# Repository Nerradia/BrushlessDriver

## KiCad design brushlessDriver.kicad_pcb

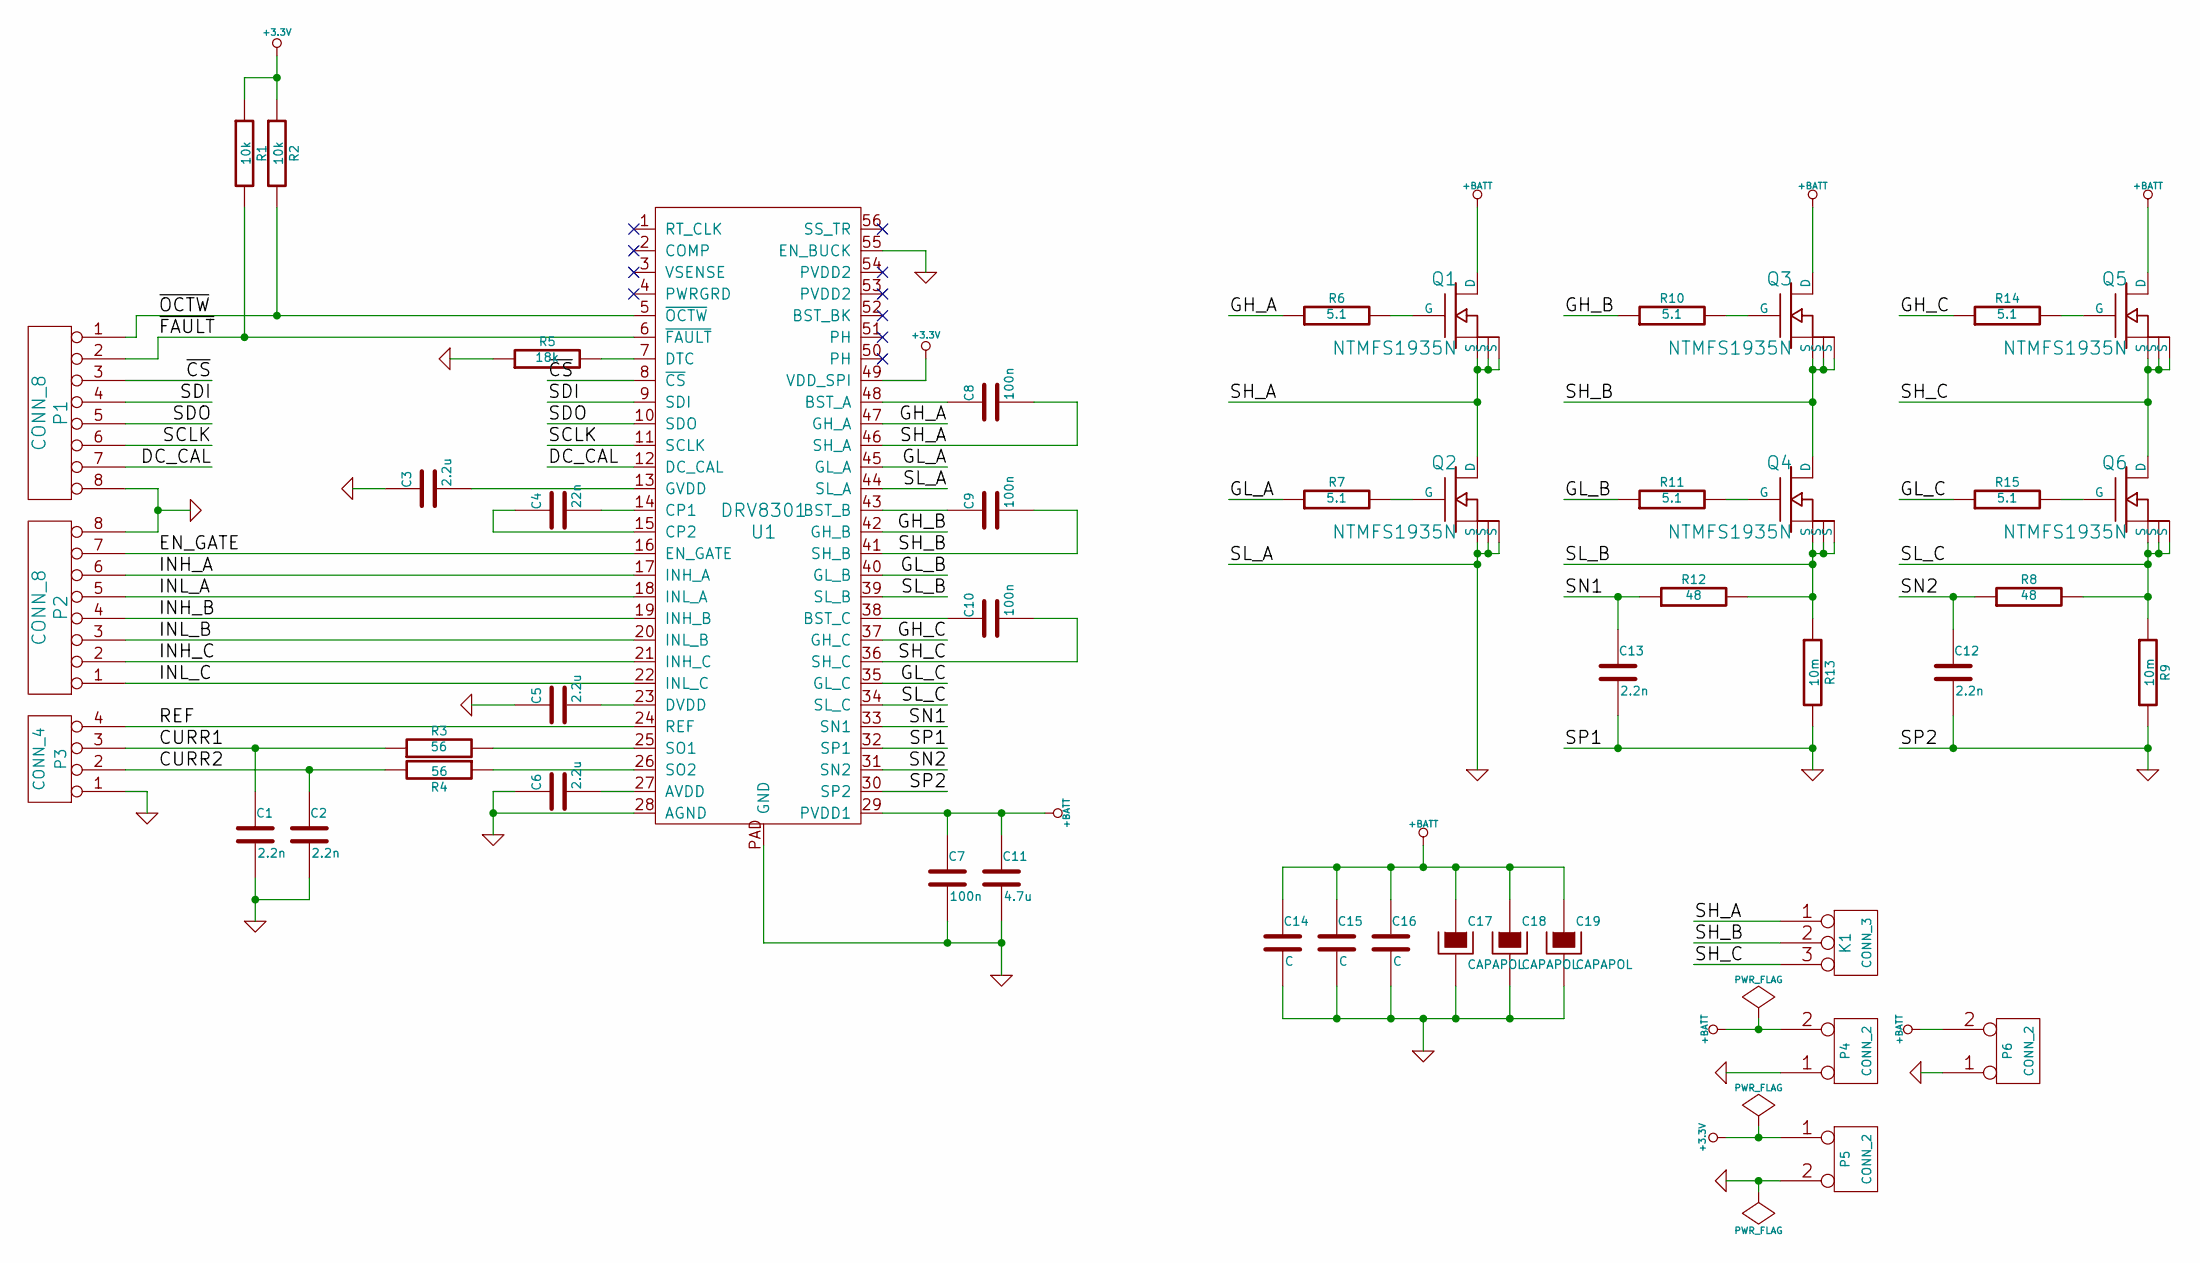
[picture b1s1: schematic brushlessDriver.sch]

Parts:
C1, C2, C12, C13: 2.2n
C3, C5, C6: 2.2u
C4: 22n
C7, C8, C9, C10: 100n
C11: 4.7u
C14, C15, C16: C
C17, C18, C19: CAPAPOL
K1: CONN_3
P1, P2: CONN_8
P3: CONN_4
P4, P5, P6: CONN_2
Q1, Q2, Q3, Q4, Q5, Q6: NTMFS1935N
R1, R2: 10k
R3, R4: 56
R5: 18k
R6, R7, R10, R11, R14, R15: 5.1
R8, R12: 48
R9, R13: 10m
U1: DRV8301

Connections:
+3.3V: P5.1, R1.1, R2.1, U1.49 (VDD_SPI)
+BATT: C7.1, C11.1, C14.1, C15.1, C16.1, C17.1, C18.1, C19.1, P4.2 (PM), P6.2 (PM), Q1.5 (D), Q3.5 (D), Q5.5 (D), U1.29 (PVDD1)
/CURR1: C1.1, P3.3, R3.1
/CURR2: C2.1, P3.2, R4.2
/DC_CAL: P1.7, U1.12 (DC_CAL)
/EN_GATE: P2.7, U1.16 (EN_GATE)
/GH_A: R6.1, U1.47 (GH_A)
/GH_B: R10.1, U1.42 (GH_B)
/GH_C: R14.1, U1.37 (GH_C)
/GL_A: R7.1, U1.45 (GL_A)
/GL_B: R11.1, U1.40 (GL_B)
/GL_C: R15.1, U1.35 (GL_C)
/INH_A: P2.6, U1.17 (INH_A)
/INH_B: P2.4, U1.19 (INH_B)
/INH_C: P2.2, U1.21 (INH_C)
/INL_A: P2.5, U1.18 (INL_A)
/INL_B: P2.3, U1.20 (INL_B)
/INL_C: P2.1, U1.22 (INL_C)
/REF: P3.4, U1.24 (REF)
/SCLK: P1.6, U1.11 (SCLK)
/SDI: P1.4, U1.9 (SDI)
/SDO: P1.5, U1.10 (SDO)
/SH_A: C8.2, K1.1, Q1.1 (S), Q1.2 (S), Q1.3 (S), Q2.5 (D), U1.46 (SH_A)
/SH_B: C9.2, K1.2 (PM), Q3.1 (S), Q3.2 (S), Q3.3 (S), Q4.5 (D), U1.41 (SH_B)
/SH_C: C10.2, K1.3, Q5.1 (S), Q5.2 (S), Q5.3 (S), Q6.5 (D), U1.36 (SH_C)
/SL_B: Q4.1 (S), Q4.2 (S), Q4.3 (S), R12.2, R13.1, U1.39 (SL_B)
/SL_C: Q6.1 (S), Q6.2 (S), Q6.3 (S), R8.2, R9.1, U1.34 (SL_C)
/SN1: C13.1, R12.1, U1.33 (SN1)
/SN2: C12.1, R8.1, U1.31 (SN2)
/~CS: P1.3, U1.8 (~CS)
/~FAULT: P1.2, R1.2, U1.6 (~FAULT)
/~OCTW: P1.1, R2.2, U1.5 (~OCTW)
GND: C1.2, C2.2, C3.1, C5.1, C6.1, C7.2, C11.2, C12.2, C13.2, C14.2, C15.2, C16.2, C17.2, C18.2, C19.2, P1.8, P2.8, P3.1, P4.1, P5.2 (PM), P6.1, Q2.1 (S), Q2.2 (S), Q2.3 (S), R5.1, R9.2, R13.2, U1.28 (AGND), U1.30 (SP2), U1.32 (SP1), U1.44 (SL_A), U1.55 (EN_BUCK), U1.PAD (GND)
unnamed: C5.2, U1.23 (DVDD)
unnamed: C4.2, U1.14 (CP1)
unnamed: C4.1, U1.15 (CP2)
unnamed: C3.2, U1.13 (GVDD)
unnamed: C6.2, U1.27 (AVDD)
unnamed: R3.2, U1.25 (SO1)
unnamed: R4.1, U1.26 (SO2)
unnamed: R5.2, U1.7 (DTC)
unnamed: Q2.4 (G), R7.2
unnamed: C10.1, U1.38 (BST_C)
unnamed: Q1.4 (G), R6.2
unnamed: C8.1, U1.48 (BST_A)
unnamed: C9.1, U1.43 (BST_B)
unnamed: Q5.4 (G), R14.2
unnamed: Q4.4 (G), R11.2
unnamed: Q6.4 (G), R15.2
unnamed: Q3.4 (G), R10.2

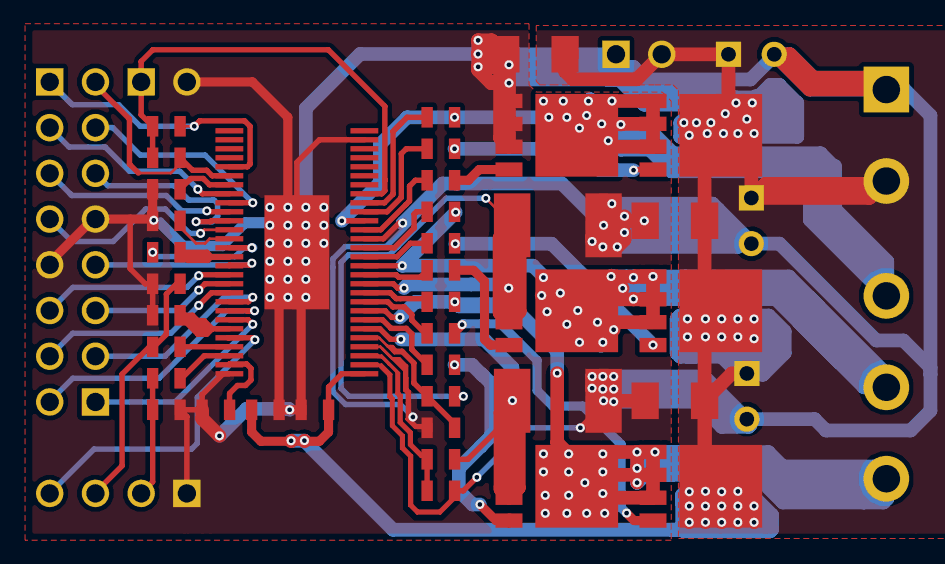
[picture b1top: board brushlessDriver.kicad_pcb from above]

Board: 2 copper layers, 48 parts (0 on the bottom side), 50 nets.

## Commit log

2017-08-14 Finished routing. Needs some inspections about ground loops and supply rails.
2018-03-30 pins
2018-06-17 Hall sensor can be read
